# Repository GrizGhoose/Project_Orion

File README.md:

# H.E.R — NASA Space Apps 2026

H.E.R is a prototype astronaut health monitoring and response system for lunar EVA. It combines a helmet HUD, a companion crew tablet, ESP32 optical measurements, a Raspberry Pi gateway, PCB engineering, and research-based demonstrations. The synchronized demonstration uses simulated physiology; the live hardware path is a separate integration. This is a concept prototype, not a medically validated or flight-ready system.

## Repository map

```text
Project_Orion/
├── apps/
│   ├── astronaut-eva-hud-ZX/          Current HUD: manual and synchronized modes
│   ├── tablet/                        Current tablet: Python, browser replay, sync
│   ├── astronaut-eva-hud-hardware/     Live Raspberry Pi HUD variant
│   └── tablet-hardware/               Separate live WebSocket/HTTP sensor variant
├── demo/                              Shared Node timeline, server, build, tests
├── firmware/esp32-vitals/              Live ESP32 measurement and MQTT firmware
├── services/raspberry-pi-gateway/       MQTT ingestion, SQLite, API, HUD hosting
├── hardware/HERBv1_PCB/                KiCad project, schematic, and PCB
├── research/
│   ├── HYPOXIA/                       Datasets, source documents, processing script
│   └── MAX30102_raw_reading-test/      Sensor bring-up and timed raw-capture tools
├── docs/                              Shared wiring, transport, measurement guides
├── .github/                           Repository-facing documentation
├── node_modules/                      Existing tracked dependency snapshot
├── .gitignore
└── README.md
```

Each application keeps its own dependencies, assets, tests, and documentation. Install dependencies inside that application's folder. The existing root dependency snapshot is retained for preservation; it is not a root npm workspace. Earlier implementations retained inside applications remain in place.

## Run the synchronized demonstration

Use a Node.js version supported by the application lockfiles (Node 24.15+ is documented for the current HUD tooling). Run from the repository root:

```powershell
npm.cmd --prefix apps/astronaut-eva-hud-ZX ci
npm.cmd --prefix apps/tablet/frontend ci
node demo/build.mjs
node demo/server.mjs
```

On macOS/Linux, use `npm` in place of `npm.cmd`. Open:

- HUD: <http://localhost:8080/hud/?sync=1>
- Tablet: <http://localhost:8080/tablet/?sync=1>

The first event-stream connection starts one shared timeline. Scenario 3 activates at 15 seconds; the existing physiology and detector reach Warning at 21.1 seconds and Critical at 23.1 seconds. The tablet's successful final **Finish** resolves the shared incident and clears both displays. Refreshes and late connections adopt the existing server session. Browser audio/fullscreen permissions still require a user gesture.

Reset locally with <http://localhost:8080/sync/reset>, or use POST:

```powershell
Invoke-RestMethod -Method Post http://localhost:8080/sync/reset
```

GET is restricted to direct loopback development requests and disabled in production. POST also supports LAN clients. For multiple devices, replace `localhost` with the host's LAN address and allow TCP 8080; keep the server awake. `PORT` overrides the server port. See the [complete demo guide](demo/README.md) for lifecycle, access rules, and verification.

## Run applications independently

### Current HUD

```powershell
npm.cmd --prefix apps/astronaut-eva-hud-ZX ci
npm.cmd --prefix apps/astronaut-eva-hud-ZX run dev
```

Open the Vite URL for manual mode. Append `?sync=1` while the demo server runs to use the shared timeline through the existing `/sync` proxy. See the [HUD guide](apps/astronaut-eva-hud-ZX/README.md).

### Current tablet

The original Python backend workflow requires Python 3.11+ and the frontend's Node/npm dependencies. On macOS/Linux or a compatible Bash environment:

```sh
./apps/tablet/run.sh
```

It builds the frontend and serves the tablet at <http://localhost:8000>. For Windows PowerShell, from the repository root:

```powershell
python -m venv apps/tablet/backend/.venv
apps/tablet/backend/.venv/Scripts/python.exe -m pip install -r apps/tablet/backend/requirements.txt
npm.cmd --prefix apps/tablet/frontend ci
npm.cmd --prefix apps/tablet/frontend run build
Set-Location apps/tablet/backend
.venv/Scripts/python.exe -m uvicorn app.server:app --host 0.0.0.0 --port 8000
```

For hot reload, run the frontend's `npm run dev` alongside the backend; `/api` and `/ws` proxy to port 8000. The dataset default is now [research/HYPOXIA](research/HYPOXIA/README.md); `HYPOXIA_DIR` still overrides it. The tablet also retains its independent browser-only replay and Vercel configuration. See the [tablet guide](apps/tablet/README.md).

The synchronized build sets different asset bases in the same output folders. Run `node demo/build.mjs` again before presenting after any standalone production build.

## Hardware, firmware, and physical engineering

- [ESP32 ↔ Raspberry Pi Wi-Fi/MQTT guide](docs/ESP32_RASPBERRY_PI_MQTT.md): wiring, broker setup, firmware transport, and two-way communication tests.
- [ESP32 firmware and startup baseline](firmware/esp32-vitals/README.md): heart rate, SpO₂, signal validity, baseline, and prototype alert decisions; one report per second with up to 90 results from the trailing 90 seconds.
- [Raspberry Pi gateway](services/raspberry-pi-gateway/README.md): persists readings/calibration sessions in SQLite, exposes the HTTP API, and serves the built live HUD on port 8200. `HUD_DIST` and `EVA_DB` overrides remain supported.
- [Hardware HUD variant](apps/astronaut-eva-hud-hardware/README.md): Pi API by default; `?demo=1` selects its retained simulator. Its development `/api` proxy uses port 8200.
- [Hardware tablet variant](apps/tablet-hardware/README.md): separate sensor WebSocket/HTTP integration on port 8100, with bundled research data. It is not automatically connected to the MQTT gateway. Its documentation retains earlier WebSocket firmware references whose implementation is absent from this checkout.
- [PCB project](hardware/HERBv1_PCB/README.md): KiCad project, schematic, board, and library requirements. Board compatibility with the development firmware is a separate engineering check.
- [Raw-sensor experiment](research/MAX30102_raw_reading-test/README.md) and [earlobe measurement protocol](docs/EARLOBE_MEASUREMENT_PROTOCOL.md): preserve the distinction between hardware bring-up, experimental captures, and live measurement firmware.

The [HYPOXIA data pack](research/HYPOXIA/README.md) retains NASA and analog data, provenance, and source documents. Its two oversized raw waveform files remain excluded. Rebuilding requires the original external raw inputs; reorganization does not require dataset regeneration.

## Team workflow

1. Pull and review shared changes before starting work; coordinate edits to the same application or firmware.
2. Work inside the relevant project, use its lockfile, and preserve the independent application variants. Keep detection rules, scenario behavior, and UI changes separate from organizational changes.
3. Keep device credentials in ignored `secrets.h` or environment files. Local virtual environments, deployment metadata, recordings, and build output stay local. Only sanitized environment examples belong in Git.
4. Run the relevant project's documented checks. For the synchronized demo, run `node --test demo/session.test.mjs demo/resetAccess.test.mjs demo/transport.test.mjs`, both HUD test/lint suites as applicable, and `node demo/build.mjs`.
5. Review the staged diff and use a pull request for team review. No commits, pushes, or deployments are performed by the reorganization itself.

Existing clones should update IDE/service working directories and deployment project roots to the new locations. Recreate virtual environments if their embedded paths are stale, and update absolute `HUD_DIST`/`HYPOXIA_DIR` settings. See [migration and preservation notes](docs/REPOSITORY_REORGANIZATION.md).

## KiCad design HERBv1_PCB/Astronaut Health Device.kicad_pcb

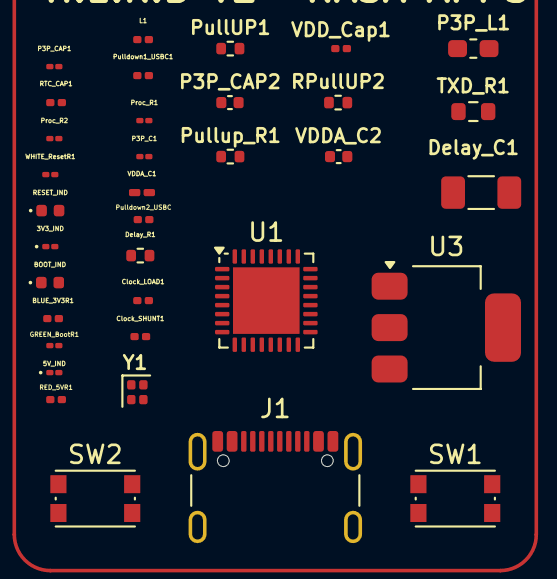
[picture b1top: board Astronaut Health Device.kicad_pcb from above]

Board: 2 copper layers, 36 parts (1 on the bottom side), 19 nets, no tracks yet.

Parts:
BLUE_3V3R1: 220; R_0201_0603Metric
Clock_LOAD1: 8pF; C_0201_0603Metric
Clock_SHUNT1: 3pF; C_0201_0603Metric
D1: 5V_IND; LED_01005_0402Metric
D2: 3V3_IND; LED_01005_0402Metric
D3: BOOT_IND; LED_0402_1005Metric
D4: RESET_IND; LED_0402_1005Metric
Delay_C1: 1uF; C_1206_3216Metric_Pad1.33x1.80mm_HandSolder
Delay_R1: 10k; R_0402_1005Metric
GREEN_BootR1: 66; R_01005_0402Metric
J1: USB_C_Receptacle_USB2.0_14P; USB_C_Receptacle_GCT_USB4105-xx-A_16P_TopMnt_Horizontal
L1: 24nH; L_0201_0603Metric
P3P_C1: 1uF; C_01005_0402Metric
P3P_CAP1: 0.1uF; C_01005_0402Metric
P3P_CAP2: 10uF; C_0402_1005Metric
P3P_L1: 2.0nH; L_0603_1608Metric_Pad1.05x0.95mm_HandSolder
Proc_R1, Proc_R2: 22; R_01005_0402Metric
PullUP1: 4.7k; R_0402_1005Metric
Pulldown1_USBC1, Pulldown2_USBC1: 5.1k; R_0201_0603Metric
Pullup_R1: 10k; R_0402_1005Metric
RED_5VR1: 300; R_0201_0603Metric
RPullUP2: 4.7k; R_0402_1005Metric
RTC_CAP1: 0.1uF; C_0201_0603Metric
SW1: Boot; SW_Push_1P1T_NO_CK_KMR2
SW2: Reset; SW_Push_1P1T_NO_CK_KMR2
TXD_R1: 499; R_0603_1608Metric
U1: ESP32-C3; QFN-32-1EP_5x5mm_P0.5mm_EP3.7x3.7mm
U2: MAX30102; Maxim_OLGA-14_3.3x5.6mm_P0.8mm
U3: LT1963AxST-3.3; SOT-223-3_TabPin2
VDDA_C1: 1uF; C_0201_0603Metric_Pad0.64x0.40mm_HandSolder
VDDA_C2: 10nF; C_0402_1005Metric
VDD_Cap1: 0.1uF; C_0201_0603Metric
WHITE_ResetR1: 22; R_01005_0402Metric
Y1: XTL911100-M118-190; Crystal_SMD_1210-4Pin_1.2x1.0mm

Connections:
+3.3V: BLUE_3V3R1.1, Delay_R1.2, P3P_CAP1.2, P3P_CAP2.2, P3P_L1.1, Pullup_R1.1, RTC_CAP1.1, U1.11 (VDD3P3_RTC), U1.17 (VDD3P3_CPU), U1.31 (VDDA), U1.32 (VDDA), U2.9 (VLED+), U2.10 (VLED+), U2.11 (VDD), U3.3 (OUT), VDDA_C1.2, VDDA_C2.2, VDD_Cap1.1
GND: Clock_LOAD1.1, Clock_SHUNT1.2, D1.1 (K), D2.1 (K), D3.1 (K), D4.1 (K), Delay_C1.1, J1.A1 (GND), J1.A5 (CC1), J1.A12 (GND), J1.B1 (GND), J1.B5 (CC2), J1.B12 (GND), J1.SH (SHIELD), P3P_C1.1, P3P_CAP1.1, P3P_CAP2.1, PullUP1.2, Pulldown1_USBC1.1, Pulldown1_USBC1.2, Pulldown2_USBC1.1, Pulldown2_USBC1.2, RPullUP2.2, RTC_CAP1.2, SW1.2, SW2.2, U1.33 (GND), U2.4 (PGND), U2.12 (GND), U3.2 (GND), VDDA_C1.1, VDDA_C2.1, VDD_Cap1.2, Y1.2 (GND), Y1.4 (GND)
unnamed: D1.2 (A), RED_5VR1.1
unnamed: BLUE_3V3R1.2, D2.2 (A)
unnamed: D3.2 (A), GREEN_BootR1.2
unnamed: D4.2 (A), WHITE_ResetR1.2
unnamed: Delay_C1.2, Delay_R1.1
unnamed: GREEN_BootR1.1, Pullup_R1.2, SW1.1
unnamed: J1.A6 (D+), J1.B6 (D+), Proc_R2.1
unnamed: J1.A7 (D-), J1.B7 (D-), Proc_R1.1
unnamed: P3P_C1.2, P3P_L1.2, U1.2 (VDD3P3), U1.3 (VDD3P3)
unnamed: SW2.1, WHITE_ResetR1.1
unnamed: PullUP1.1, U1.10 (MTDI)
unnamed: RPullUP2.1, U1.9 (MTMS)
unnamed: TXD_R1.2, U1.28 (U0TXD)
unnamed: Clock_SHUNT1.1, U1.29 (XTAL_N), Y1.3 (XOUT)
unnamed: L1.2, U1.30 (XTAL_P)
unnamed: J1.A4 (VBUS), J1.A9 (VBUS), J1.B4 (VBUS), J1.B9 (VBUS), RED_5VR1.2, U3.1 (IN)
unnamed: Clock_LOAD1.2, L1.1, Y1.1 (XIN)
